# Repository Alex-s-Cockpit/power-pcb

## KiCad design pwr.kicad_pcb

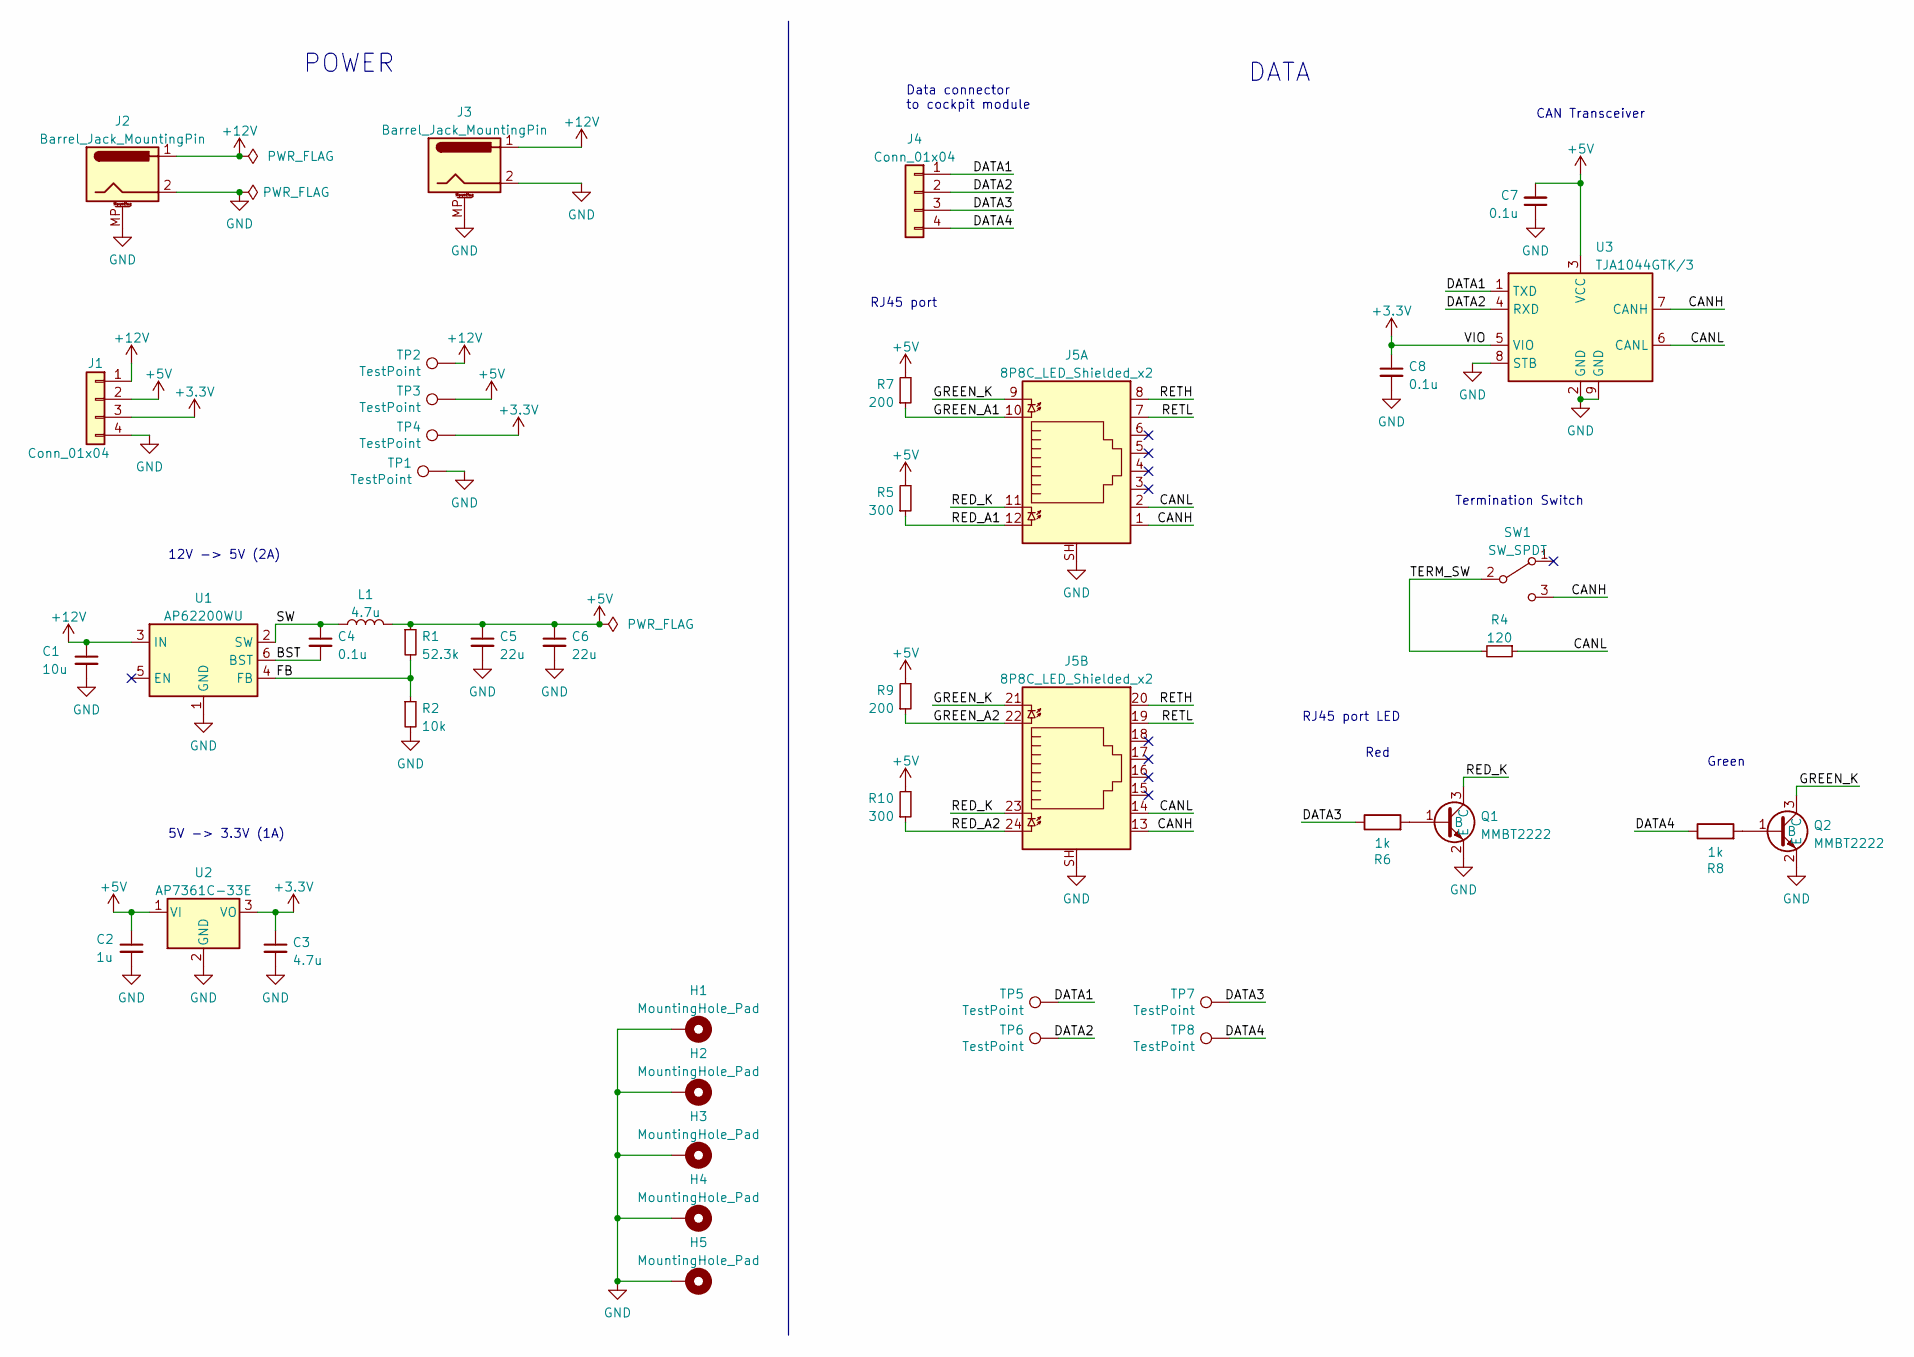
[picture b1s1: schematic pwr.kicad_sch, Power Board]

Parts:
C1: 10u; C_0805_2012Metric
C2: 1u; C_0805_2012Metric
C3: 4.7u; C_0805_2012Metric
C4, C7, C8: 0.1u; C_0805_2012Metric
C5, C6: 22u; C_1210_3225Metric
H1, H2, H3, H4, H5: MountingHole_Pad; MountingHole_2.2mm_M2_ISO7380_Pad
J1: Conn_01x04; JST_XH_S4B-XH-A-1_1x04_P2.50mm_Horizontal
J2, J3: Barrel_Jack_MountingPin; BarrelJack_Horizontal
J4: Conn_01x04; JST_PH_B4B-PH-K_1x04_P2.00mm_Vertical
J5: 8P8C_LED_Shielded_x2; RJ45_Amphenol_RJHSE538X-02
L1: 4.7u; L_Wuerth_WE-PD-Typ-LS_Handsoldering
Q1, Q2: MMBT2222; SOT-23
R1: 52.3k; R_0805_2012Metric
R2: 10k; R_0805_2012Metric
R4: 120; R_0805_2012Metric
R5, R10: 300; R_0805_2012Metric
R6, R8: 1k; R_0805_2012Metric; mouser# 603-RC0805FR-071KL
R7, R9: 200; R_0805_2012Metric
SW1: SW_SPDT; SW_CuK_OS102011MA1QN1_SPDT_Angled
TP1, TP2, TP3, TP4, TP5, TP6, TP7, TP8: TestPoint; TestPoint_THTPad_D1.5mm_Drill0.7mm
U1: AP62200WU; TSOT-23-6
U2: AP7361C-33E; SOT-223-3_TabPin2
U3: TJA1044GTK/3; DFN-8-1EP_3x3mm_P0.65mm_EP1.55x2.4mm

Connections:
+3.3V: C3.1, C8.1, J1.3, TP4.1, U2.3 (VO), U3.5 (VIO)
+5V: C2.1, C5.1, C6.1, C7.2, J1.2, L1.2, R1.1, R5.2, R7.2, R9.2, R10.2, TP3.1, U2.1 (VI), U3.3 (VCC)
+12V: C1.1, J1.1, J2.1, J3.1, TP2.1, U1.3 (IN)
/BST: C4.2, U1.6 (BST)
/CANH: J5.1, J5.13, SW1.3 (C), U3.7 (CANH)
/CANL: J5.2, J5.14, R4.1, U3.6 (CANL)
/DATA1: J4.1, TP5.1, U3.1 (TXD)
/DATA2: J4.2, TP6.1, U3.4 (RXD)
/DATA3: J4.3, R6.1, TP7.1
/DATA4: J4.4, R8.1, TP8.1
/FB: R1.2, R2.1, U1.4 (FB)
/GREEN_A1: J5.10, R7.1
/GREEN_A2: J5.22, R9.1
/GREEN_K: J5.9, J5.21, Q2.3 (C)
/RED_A1: J5.12, R5.1
/RED_A2: J5.24, R10.1
/RED_K: J5.11, J5.23, Q1.3 (C)
/RETH: J5.8, J5.20
/RETL: J5.7, J5.19
/SW: C4.1, L1.1, U1.2 (SW)
/TERM_SW: R4.2, SW1.2 (B)
GND: C1.2, C2.2, C3.2, C5.2, C6.2, C7.1, C8.2, H1.1, H2.1, H3.1, H4.1, H5.1, J1.4, J2.2, J2.MP (MountPin), J3.2, J3.MP (MountPin), J5.SH, Q1.2 (E), Q2.2 (E), R2.2, TP1.1, U1.1 (GND), U2.2 (GND), U3.2 (GND), U3.8 (STB), U3.9 (GND)
unnamed: Q1.1 (B), R6.2
unnamed: Q2.1 (B), R8.2

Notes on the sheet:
RJ45 port
CAN Transceiver
POWER
Data connector to cockpit module
DATA
5V -> 3.3V (1A)
RJ45 port LED
12V -> 5V (2A)
Green
Red
Termination Switch

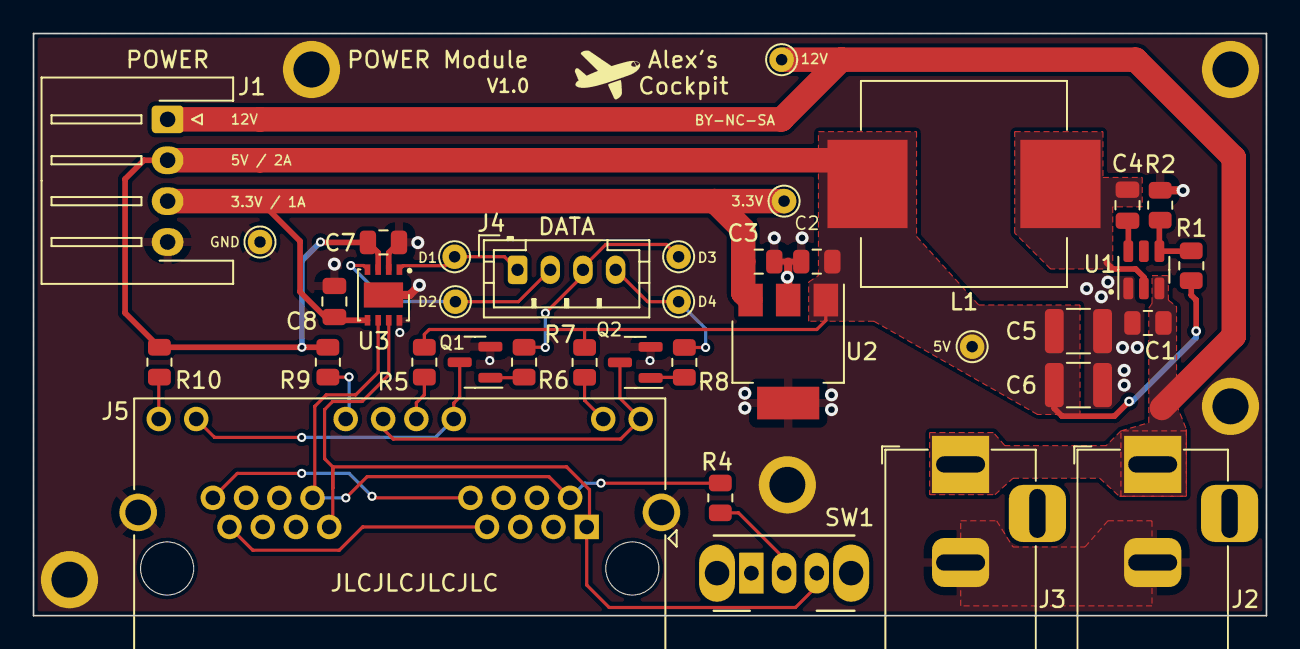
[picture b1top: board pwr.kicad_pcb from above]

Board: 2 copper layers, 75.4 x 35.6 mm, 42 parts (0 on the bottom side), 24 nets.

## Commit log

2022-11-14 Initial import

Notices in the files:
pwr.kicad_sch:
CC BY-NC-SA
